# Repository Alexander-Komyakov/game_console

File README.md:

## Игровая консоль

Игровая консоль включает в себя:
 - Схему платы в проекте KiCad
 - 3Д модель
 - программное обеспечение https://gitlab.3dprintlite.ru/esp32/dt240x320

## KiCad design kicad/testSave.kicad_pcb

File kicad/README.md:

Для изготовления печатной платы я использовал CNC 3018 MAX, полностью металлическую версию.

`Версия KiCad 9.0.0-9.0.0-2 ubuntu 24`

На основной плате видно, что мы используем ESP32-WROOM-32 с 520кб ОЗУ и 4мб FLASH.

К ней подключен по SPI ST7789V 240x320, шлейфом 18 пин, 5-ти позиционной кнопке и четырем обычным кнопкам.
Для получения дисплея как в нашем проекте нужно снять с красной платы дисплей для этого.
Будьте осторожны, шлейф очень хрупкий. Лучше работать феном и медленно, без большой нагрузки отодвигать шлейф со своего посадочного места для дальнейшего закрепления на нашей печатной плате.

Для сборки понадобится:
 - Текстолит односторонний больше чем 130x60мм
 - ESP32-WROOM-32 4мб flash, 520 КБ ОЗУ без PSRAM
 - TP4056
 - Аккумулятор 1000мач, 3.7В https://aliexpress.ru/item/4000939317595.html?sku_id=10000011329056470&spm=a2g2w.productlist.search_results.0.2c3a1aecBi4K3i

 - Тактовые кнопки, 4 шт. Размер: 12*12*7,3 мм

 - Пяти позиционная кнопка https://aliexpress.ru/item/1005008348341984.html?sku_id=12000044686793517&spm=a2g2w.productlist.search_results.5.2bd063f3eioFhZ

 - Переключатель питания https://www.ozon.ru/product/vyklyuchatel-dvizhkovyy-polzunkovyy-pereklyuchatel-10-sht-1323063165/?from=share_android&perehod=smm_share_button_productpage_link

`Версия pcb2gcode`

```
pcb2gcode --version
2.5.0
Git commit:
Boost: 107400
Gerbv: 2.10.0
Geos: Not installed
```

Конфиг лежит в config.ini

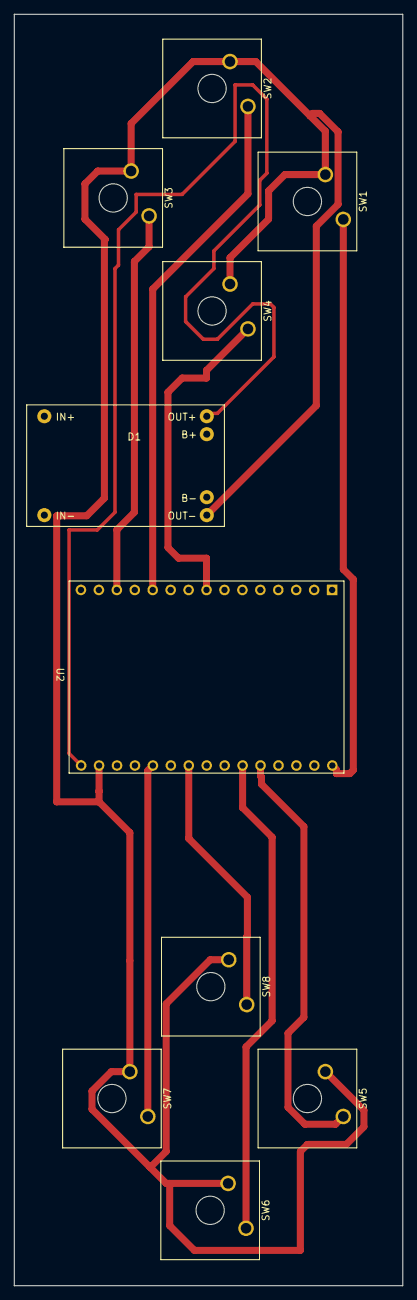
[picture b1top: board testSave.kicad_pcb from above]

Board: 2 copper layers, 55.0 x 180.0 mm, 10 parts (0 on the bottom side), 8 nets.

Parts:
D1: TP4056-Module
SW1, SW2, SW3, SW4, SW5, SW6, SW7, SW8: SW_Push; SW_Cherry_MX_1.00u_Plate
U2: ESP32-S3-WROOM-1; ESP32-Wroom-32

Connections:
unnamed: D1.3, U2.16 (IO46), U2.26 (IO45)
unnamed: D1.4, SW1.2, SW2.2, SW3.2, SW4.2, SW5.2, SW6.2, SW7.2, SW8.2, U2.1 (GND), U2.GND
unnamed: SW2.1, U2.19 (IO11)
unnamed: SW1.1, U2.21 (IO13)
unnamed: SW7.1, U2.22 (IO14)
unnamed: SW8.1, U2.25 (IO48)
unnamed: SW5.1, U2.14 (USB_D+)
unnamed: SW6.1, U2.13 (USB_D-)

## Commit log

2025-04-15 init game console
2025-04-15 add readme & remove bolt
2025-04-15 add kicad
2025-04-15 add photo
2025-04-18 update scheme; add gnd tp4056 button
2025-07-10 slim version
2025-07-15 update plate
2025-07-15 pcb2gcode add
2025-07-31 update kicad plate
2025-08-01 fix plate
2025-09-03 update kicad scheme version. Add EN to 3V3 drill and jtag change to uart
2025-09-09 add more text in kicad
